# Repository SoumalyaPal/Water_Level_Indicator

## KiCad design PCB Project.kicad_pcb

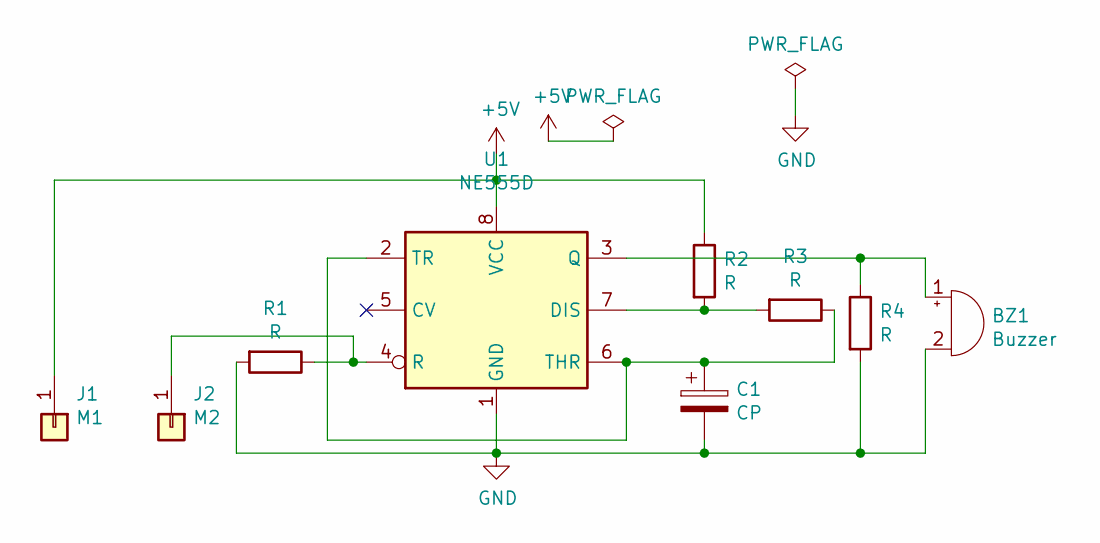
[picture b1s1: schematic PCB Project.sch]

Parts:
BZ1: Buzzer; MagneticBuzzer_Kingstate_KCG0601
C1: CP; CP_Radial_D4.0mm_P2.00mm
J1: M1; Banana_Jack_1Pin
J2: M2; Banana_Jack_1Pin
R1, R2, R3, R4: R; R_Axial_DIN0204_L3.6mm_D1.6mm_P7.62mm_Horizontal
U1: NE555D; SOIC-8_3.9x4.9mm_P1.27mm

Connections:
+5V: J1.1, R2.1, U1.8 (VCC)
GND: BZ1.2 (+), C1.2, R1.2, R4.2, U1.1 (GND)
unnamed: BZ1.1 (-), R4.1, U1.3 (Q)
unnamed: C1.1, R3.1, U1.2 (TR), U1.6 (THR)
unnamed: J2.1, R1.1, U1.4 (R)
unnamed: R2.2, R3.2, U1.7 (DIS)

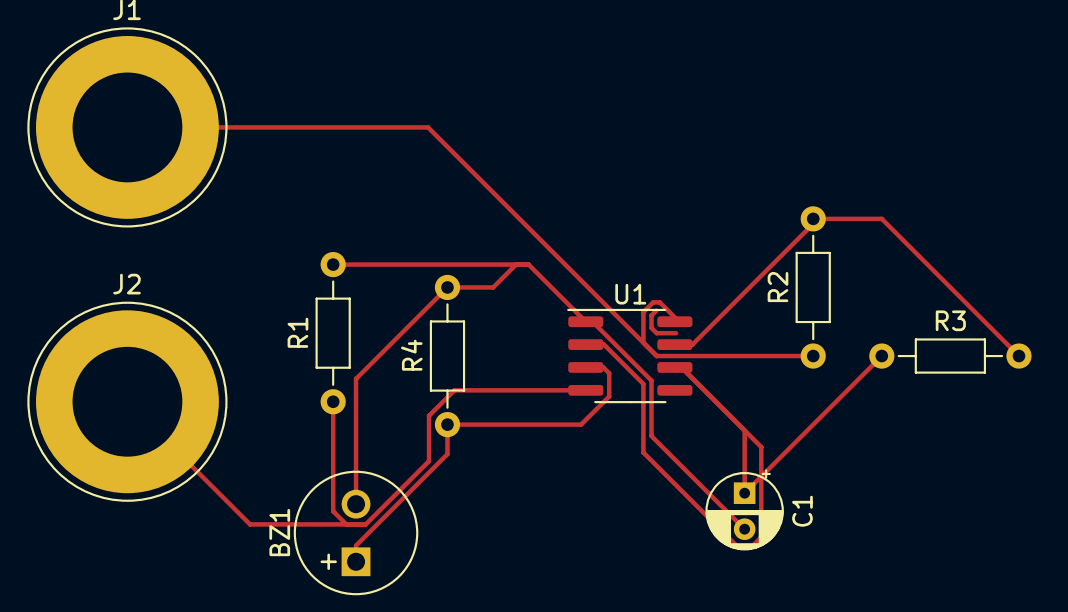
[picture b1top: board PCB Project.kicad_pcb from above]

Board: 2 copper layers, 9 parts (0 on the bottom side), 6 nets.
